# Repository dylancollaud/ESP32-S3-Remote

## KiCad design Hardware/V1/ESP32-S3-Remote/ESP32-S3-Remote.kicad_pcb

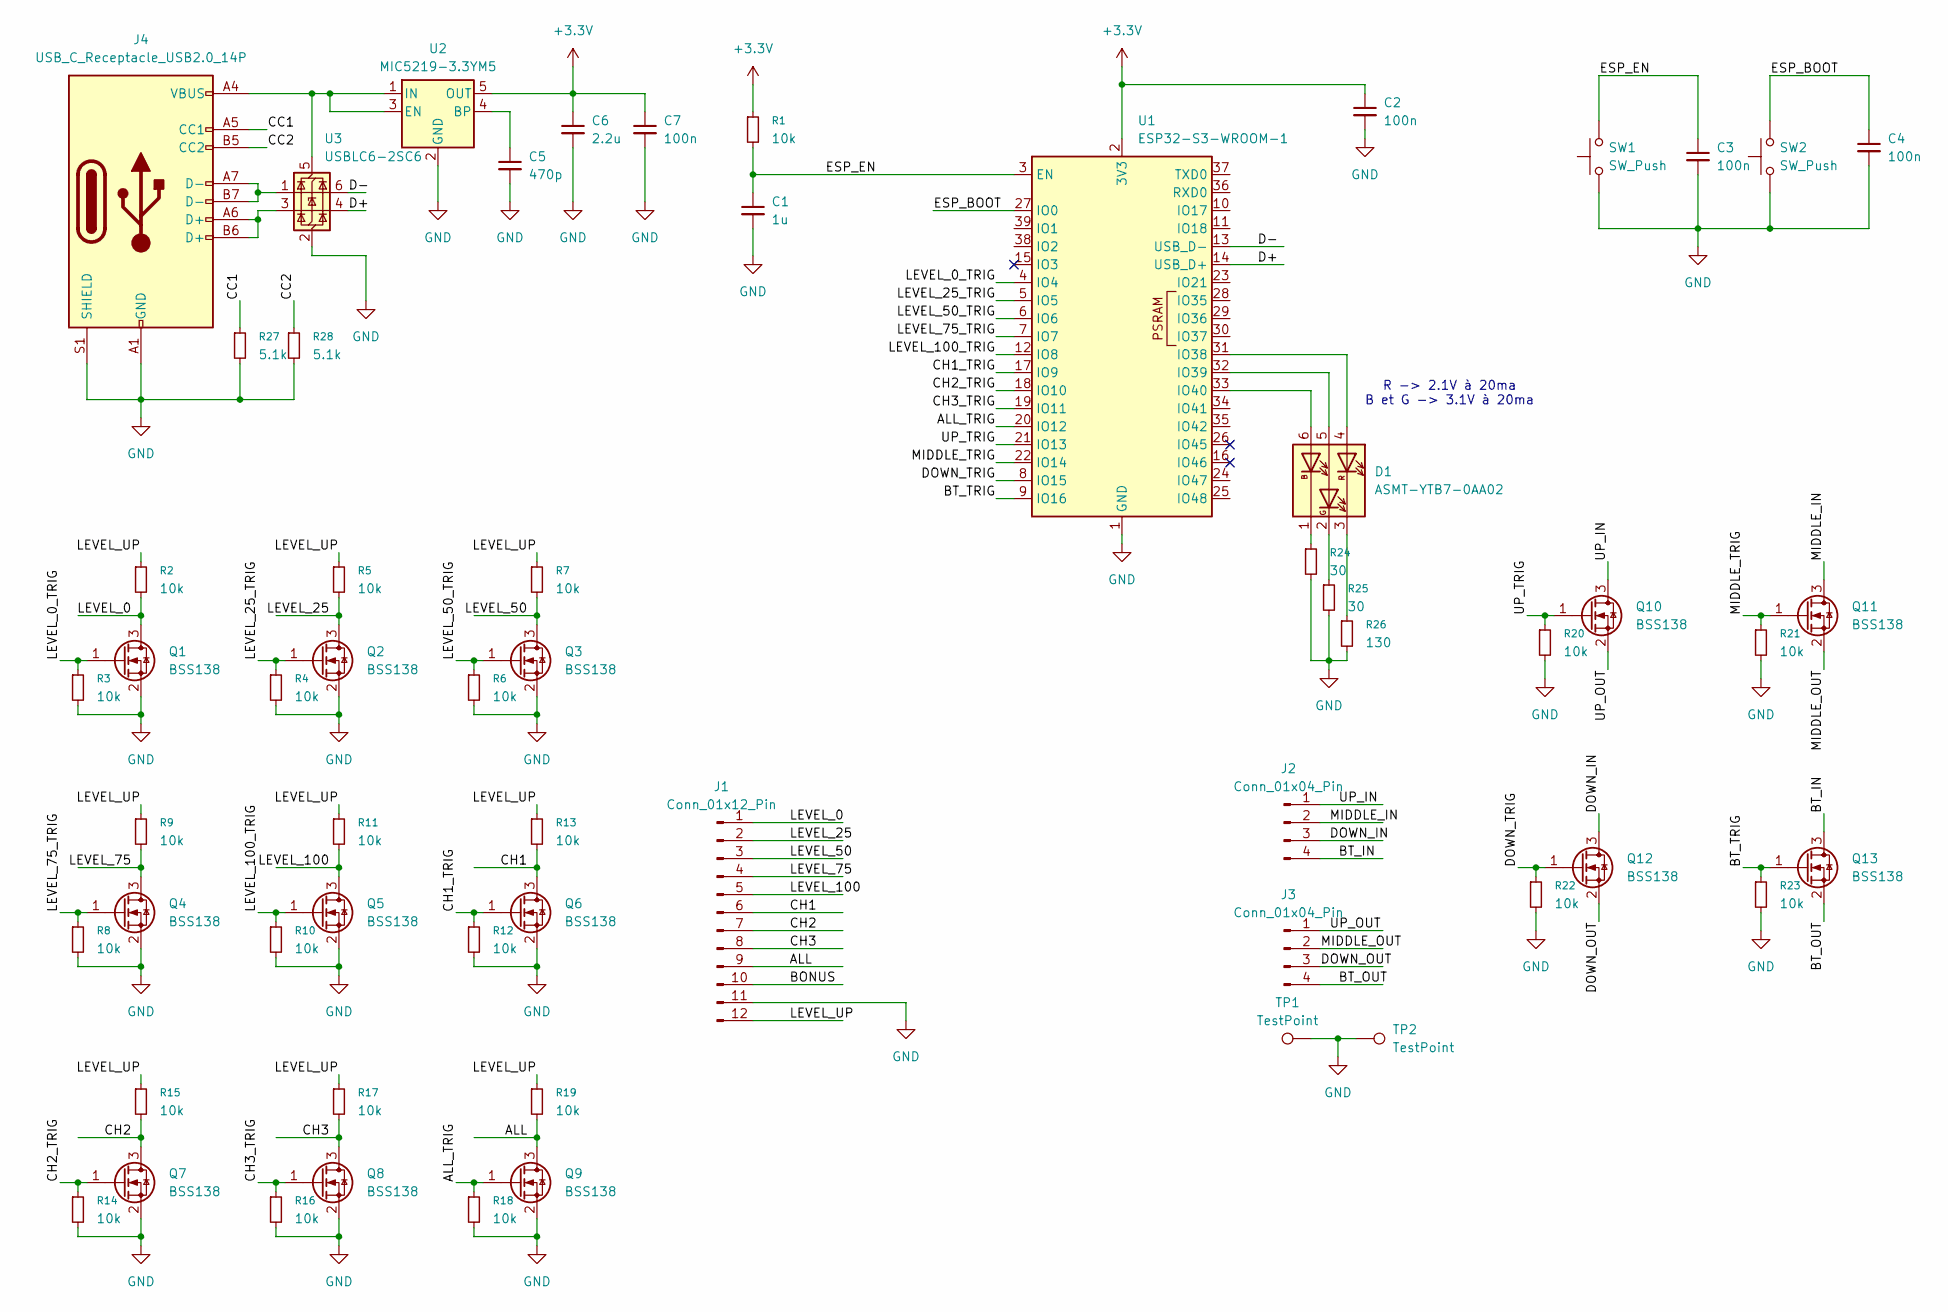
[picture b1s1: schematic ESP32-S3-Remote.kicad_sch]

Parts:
C1: 1u; C_0603_1608Metric
C2, C3, C4, C7: 100n; C_0603_1608Metric
C5: 470p; C_0603_1608Metric
C6: 2.2u; C_0603_1608Metric
D1: ASMT-YTB7-0AA02; LED_Avago_PLCC6_3x2.8mm
J1: Conn_01x12_Pin; PinHeader_1x12_P1.27mm_Vertical
J2, J3: Conn_01x04_Pin; PinHeader_1x04_P1.27mm_Vertical
J4: USB_C_Receptacle_USB2.0_14P; USB_C_Receptacle_GCT_USB4110
Q1, Q2, Q3, Q4, Q5, Q6, Q7, Q8, Q9, Q10, Q11, Q12, Q13: BSS138; SOT-23
R1, R2, R3, R4, R5, R6, R7, R8, R9, R10, R11, R12, R13, R14, R15, R16, R17, R18, R19, R20, R21, R22, R23: 10k; R_0603_1608Metric
R24, R25: 30; R_0603_1608Metric
R26: 130; R_0603_1608Metric
R27, R28: 5.1k; R_0603_1608Metric
SW1, SW2: SW_Push; SW_SPST_B3U-1000P
TP1, TP2: TestPoint; TestPoint_Pad_D1.5mm
U1: ESP32-S3-WROOM-1
U2: MIC5219-3.3YM5; SOT-23-5
U3: USBLC6-2SC6; SOT-23-6

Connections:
+3.3V: C2.1, C6.1, C7.1, R1.1, U1.2 (3V3), U2.5 (OUT)
/ALL: J1.9, Q9.3 (D), R19.2
/ALL_TRIG: Q9.1 (G), R18.1, U1.20 (IO12)
/BONUS: J1.10
/BT_IN: J2.4, Q13.3 (D)
/BT_OUT: J3.4, Q13.2 (S)
/BT_TRIG: Q13.1 (G), R23.1, U1.9 (IO16)
/CC1: J4.A5 (CC1), R27.1
/CC2: J4.B5 (CC2), R28.1
/CH1: J1.6, Q6.3 (D), R13.2
/CH1_TRIG: Q6.1 (G), R12.1, U1.17 (IO9)
/CH2: J1.7, Q7.3 (D), R15.2
/CH2_TRIG: Q7.1 (G), R14.1, U1.18 (IO10)
/CH3: J1.8, Q8.3 (D), R17.2
/CH3_TRIG: Q8.1 (G), R16.1, U1.19 (IO11)
/D+: U1.14 (USB_D+), U3.4 (I/O2)
/D-: U1.13 (USB_D-), U3.6 (I/O1)
/DOWN_IN: J2.3, Q12.3 (D)
/DOWN_OUT: J3.3, Q12.2 (S)
/DOWN_TRIG: Q12.1 (G), R22.1, U1.8 (IO15)
/ESP_BOOT: C4.1, SW2.2, U1.27 (IO0)
/ESP_EN: C1.1, C3.1, R1.2, SW1.2, U1.3 (EN)
/LEVEL_0: J1.1, Q1.3 (D), R2.2
/LEVEL_0_TRIG: Q1.1 (G), R3.1, U1.4 (IO4)
/LEVEL_25: J1.2, Q2.3 (D), R5.2
/LEVEL_25_TRIG: Q2.1 (G), R4.1, U1.5 (IO5)
/LEVEL_50: J1.3, Q3.3 (D), R7.2
/LEVEL_50_TRIG: Q3.1 (G), R6.1, U1.6 (IO6)
/LEVEL_75: J1.4, Q4.3 (D), R9.2
/LEVEL_75_TRIG: Q4.1 (G), R8.1, U1.7 (IO7)
/LEVEL_100: J1.5, Q5.3 (D), R11.2
/LEVEL_100_TRIG: Q5.1 (G), R10.1, U1.12 (IO8)
/LEVEL_UP: J1.12, R2.1, R5.1, R7.1, R9.1, R11.1, R13.1, R15.1, R17.1, R19.1
/MIDDLE_IN: J2.2, Q11.3 (D)
/MIDDLE_OUT: J3.2, Q11.2 (S)
/MIDDLE_TRIG: Q11.1 (G), R21.1, U1.22 (IO14)
/UP_IN: J2.1, Q10.3 (D)
/UP_OUT: J3.1, Q10.2 (S)
/UP_TRIG: Q10.1 (G), R20.1, U1.21 (IO13)
GND: C1.2, C2.2, C3.2, C4.2, C5.2, C6.2, C7.2, J1.11, J4.A1 (GND), J4.A12 (GND), J4.B1 (GND), J4.B12 (GND), J4.S1 (SHIELD), Q1.2 (S), Q2.2 (S), Q3.2 (S), Q4.2 (S), Q5.2 (S), Q6.2 (S), Q7.2 (S), Q8.2 (S), Q9.2 (S), R3.2, R4.2, R6.2, R8.2, R10.2, R12.2, R14.2, R16.2, R18.2, R20.2, R21.2, R22.2, R23.2, R24.2, R25.2, R26.2, R27.2, R28.2, SW1.1, SW2.1, TP1.1, TP2.1, U1.1 (GND), U1.40 (GND), U1.41 (GND), U2.2 (GND), U3.2 (GND)
unnamed: D1.6 (AB), U1.33 (IO40)
unnamed: D1.5 (AG), U1.32 (IO39)
unnamed: D1.4 (AR), U1.31 (IO38)
unnamed: D1.1 (KB), R24.1
unnamed: D1.2 (KG), R25.1
unnamed: D1.3 (KR), R26.1
unnamed: J4.A6 (D+), J4.B6 (D+), U3.3 (I/O2)
unnamed: J4.A7 (D-), J4.B7 (D-), U3.1 (I/O1)
unnamed: C5.1, U2.4 (BP)
unnamed: J4.A4 (VBUS), J4.A9 (VBUS), J4.B4 (VBUS), J4.B9 (VBUS), U2.1 (IN), U2.3 (EN), U3.5 (VBUS)

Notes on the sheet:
R -> 2.1V à 20ma B et G -> 3.1V à 20ma

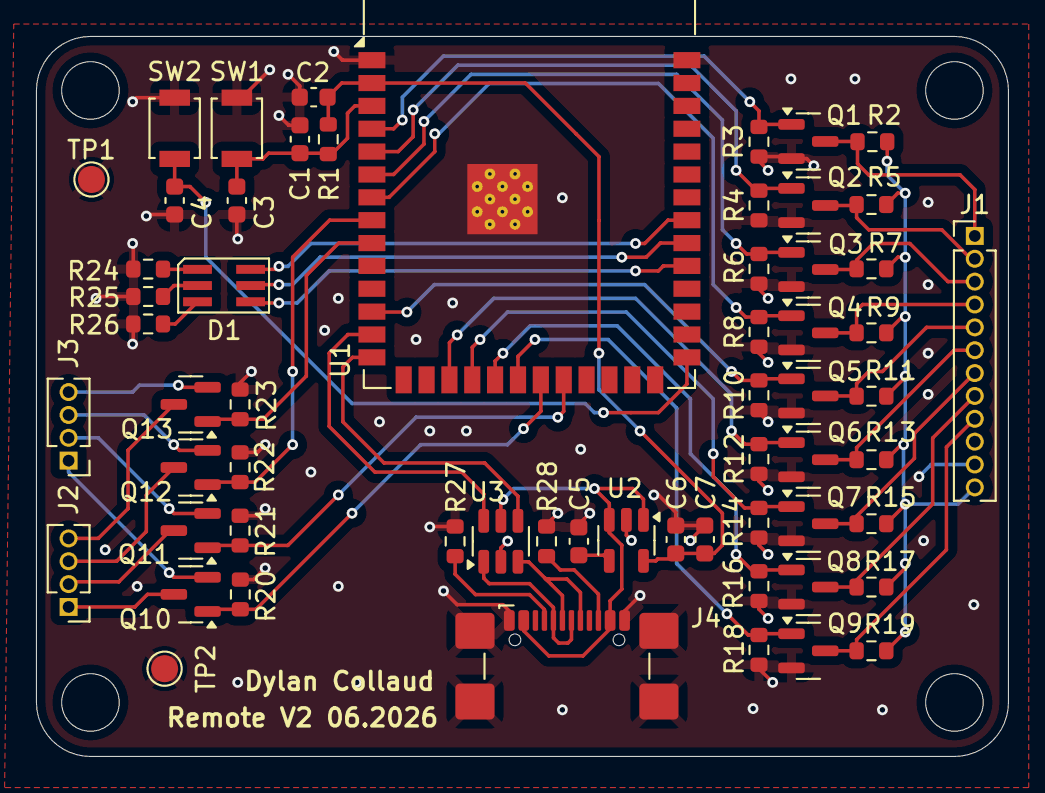
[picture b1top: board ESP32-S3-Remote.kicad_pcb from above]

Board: 2 copper layers, 54.0 x 40.0 mm, 60 parts (0 on the bottom side), 49 nets.

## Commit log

2026-06-08 New PCB
2026-06-09 Make layout
2026-06-10 Order files
2026-06-17 Add Test FW
